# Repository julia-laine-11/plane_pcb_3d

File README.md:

top view (smt leds & resistors and thru hole resistor holes)

side view (no electronics here)

I ordered them 12/8/24 and they were shipped 12/12/24

They arrived 12/23/24 (very fast!)

I began by adding all the thru hole components on the bottom side of the horizontal piece. The bottom LEDs face forward. Afterwards, I added the surface mount LEDs on the back. I forgot that I didn't have any green 0603s, so I (safely) stole some from a nearby battery pack that was no longer in use. Unfortunately, I lost all but 1 from the very windy reflow station at home. 

Honestly, that was okay though since I really only needed 1 for my dad. I figure I'll give the other 4 as random gifts to my aerospace friends or something.

I then tested it of course, because I desperately wanted to see it, and I was also super nervous I put the 0603 LEDs in backwards since they're so tiny.

(I did put the green LED in backwards once, but I flipped it around and it lit up)

To power it, I used CR2032 batteries with a small piece of tin spot welded onto each side

About now, I realized I forgot to add a switch. I had always intended to glue the battery on, but I'm not sure why I never thought of the switch. 

To power it on I attached small wires onto a potentiometer between the battery + and the PCB. After gluing both the battery and the pot on, I realized that was not going to work since the red SMT LED was always on. 

I went and found a button and replaced the pot.

It isn't ideal or the prettiest, but it is hidden on the bottom :)

I am happy with these results, but there's definitely room for improvement. If I manufacture these again I will definitely add a switch. I also might consider making the slits on each piece a tiny bit wider since there was some minor sanding I had to do. I am not sure if I would do this or not because the pieces fit so nicely after I gently tapped them together with a harder object.

I will also definitely increase the distance of the resistor holes. They were the right size and hold the resistors, but it was a little annoying to bend the wires nicely for them to fit. If the holes were slightly farther apart, they would fit so much better.

I did like how the + and - were on either side of the vertical piece. It made it easier to put the battery in place and not worry about covering up a port. It also let me place a button in and keep the wires relatively short. I would add a small hole or indent for the wire in the future though if I do keep the + on the opposite side. I can also just add a + and - to both sides so I can decide what to do depending on my materials. The school typically has everything I need, but if I am at home I might not have everything.

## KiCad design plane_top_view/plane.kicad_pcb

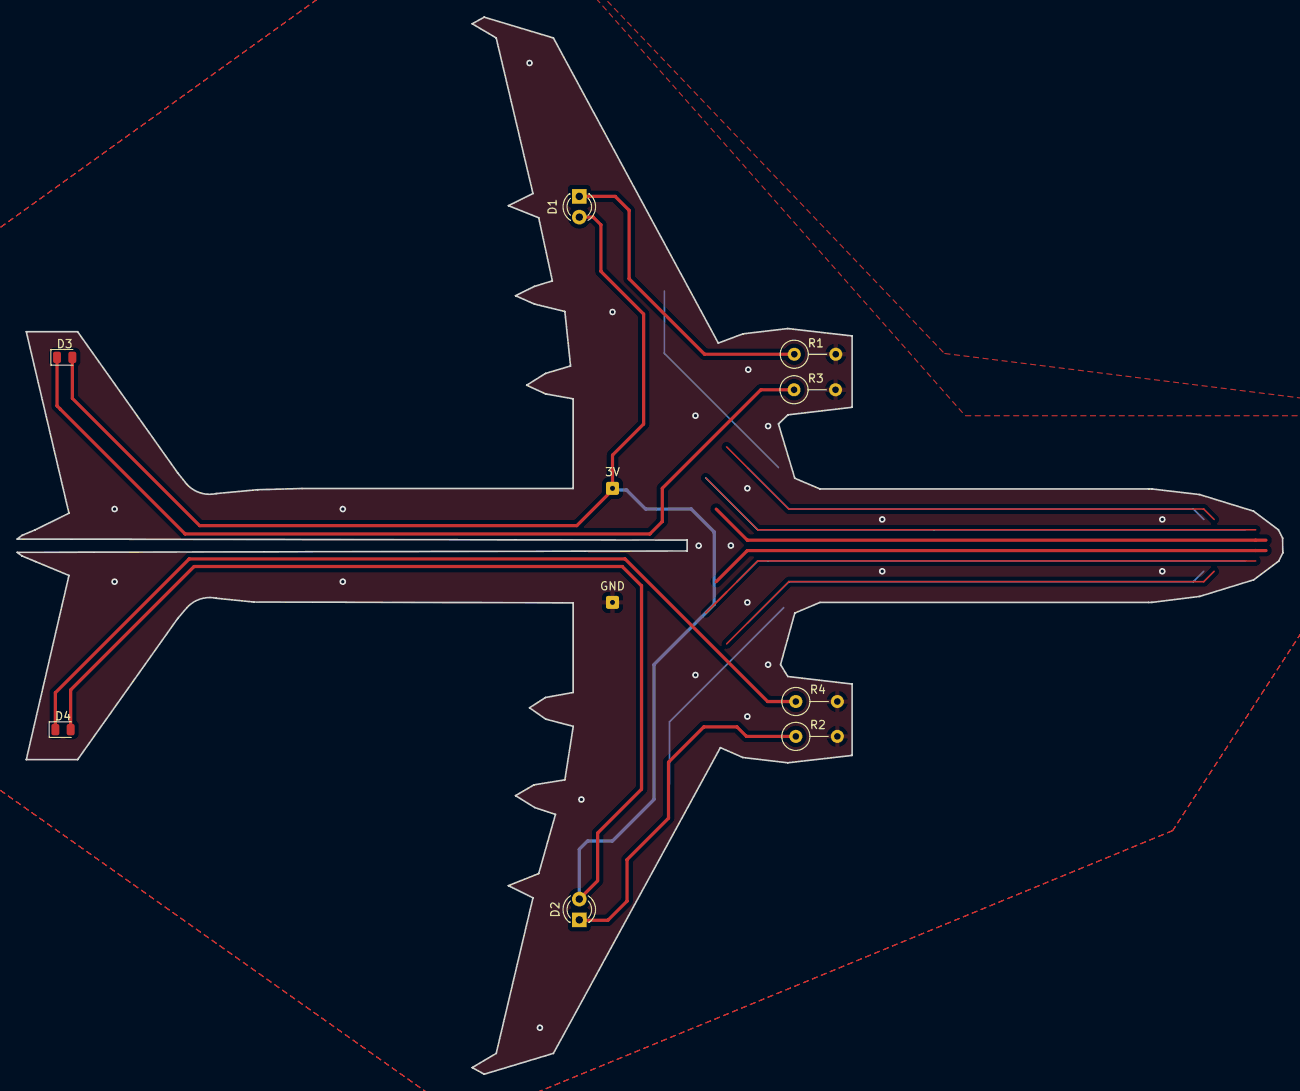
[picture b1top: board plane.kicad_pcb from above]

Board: 2 copper layers, 155.0 x 129.4 mm, 10 parts (0 on the bottom side), 6 nets.

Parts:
3V: 3v; SolderWire-0.1sqmm_1x01_D0.4mm_OD1mm
D1, D2: TSAL4400; LED_D3.0mm_IRBlack
D3, D4: LED; LED_0805_2012Metric
GND: GND; SolderWire-0.1sqmm_1x01_D0.4mm_OD1mm
R1, R2, R3, R4: RC0201FR-0710KL; R_Axial_DIN0309_L9.0mm_D3.2mm_P5.08mm_Vertical

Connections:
+3V0: 3V.1, D1.2 (A), D2.2 (A), D3.2 (A), D4.2 (A)
GND: GND.1, R1.2, R2.2, R3.2, R4.2
unnamed: D1.1 (K), R1.1
unnamed: D2.1 (K), R2.1
unnamed: D3.1 (K), R3.1
unnamed: D4.1 (K), R4.1

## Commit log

2024-11-15 uploaded plane kicad project
2024-11-15 organized into folders
2024-11-15 changed folders
2024-11-15 made it less jank
2024-11-15 made it actually have connected grounds
2024-11-15 fixed my many mistakes
    for some reason I got locked out of the file. so i just saved the files again and then moved them to the repo
2024-11-15 reorganized and verified
2024-11-15 finalized stuff
2024-12-24 Update README.md since i got the pcbs!
